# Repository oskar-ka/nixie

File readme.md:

# Features
- 6x IN-8
- 2/4x NE-2
- GPS disciplined, temperature compensated crystal oscillator
- Lysnetspænding i EU kan lovligt variere mellem 207Vac til 253Vac, som giver halveret DC på 146-182Vdc
- Automatisk lysstyrkedæmpning
- Temperaturføler
- Komponenter skal virke ved 85C (varm dag &leq;40C+4W*10K/W=80C)

# Strømforsyning
Nixie uret skal bruge to spændinger for at fungere: 5Vdc til microcontroller og logiske kredse, samt 180Vdc til at trække nixierørene. Hvert rør kan tåle op til 3.5mA, så med 6 rør skal strømforsyningen levere 21mA + lidt til de 4 små nixie prikker, så i alt maks. 30mA v. 180Vdc. Det er nok ikke nødvendigt med PFC ved 30mA, men det kunne måske være sjovt at lave hvis der er plads til det. Evt. kan strøforsyningen blive lavet på et separat print, som kan placeres under nixie-printet, så burde der være masser af plads. Skal den kunne skifte mellem 230Vac og 120Vac, og skal den gøre det automatisk?

### Specifikationer
- Fra IN-8 datablad:
    - Ignition voltage: &leq; 170V
    - Indication current: &leq; 2.5mA
    - Turn-off voltage: ??
- NE-2 lampe:
    - &lt;1mA
- 180Vdc, 20mA
- Current limiting, [foldback](https://www.eeeguide.com/foldback-current-limiting-circuit/)

### Der findes mange forskellige måder at opnå disse to spændinger:
- 12/24Vdc indgang &rarr; DC-DC til 5V + boost converter til 180Vdc
    - [Recom R12-150B](https://www.tme.eu/dk/en/details/r12-150b/dc-dc-converters/recom/)
- 230Vac indgang &rarr; diodebro som giver 325Vdc, med den rigtige modstand før 
nixierørene kan denne spænding bruges direkte; 5V AC-DC
    - Rimelig ueffektivt og ikke så sejt, men meget nemt
    - Nixiestrøm afhængig af netspænding
- 230Vac &rarr; styret thyristorbro som giver 180Vdc direkte; 5V AC-DC
    - Thyristorbroer er som regel store, ved ikke om man kan få en i DIP
- 230Vac &rarr; styret MOSFET ensretter som giver 180Vdc direkte; 5V AC-DC
    - Mere effektiv end thyristorbro
    - Skal bruge to MOSFETS hver vej for at kunne blokere = 8 MOSFETS
    - Kan evt. også laves som halvbølgeensretter, da den ikke skal levere ret meget strøm
- ~~230Vac &rarr; halveringstransformer 230V&rarr;115Vac &rarr; ensretter (styret/ikke styret); & 5V AC-DC~~
    - ~~Ret nemt, få komponenter, ret effektivt, galvanisk adskillelse~~
    - ~~Giver 160Vdc v. 230Vac, hvilket er fint, men hvis nettet går ned til 207Vdc så har vi kun 146Vdc hvilket ikke helt er nok~~
- 230Vac &rarr; 2/3-transformer = 195/217/239Vdc (min, nom, max)
    - enten direkte til nixierør, kunne sikkert fungere
        - Her vil varmetab være i modstande og måske IC, bedre at have det centreret i en NPN med varmeplade
    - eller transistor med varmetab
        - skal smide mellem 15-59V
        - ved 20mA &rarr; 0.3W-1.2W
        - TO-92: [PHE13003A](https://mou.sr/43Gdbwc) 60K/W, nogle af dem måske op til 2W??
        - TO-252 [MJD340](https://mou.sr/4o38ar5): 8.3K/W op til 15W
        - TO-220 [BUL741](https://mou.sr/3Q8gnh7): 2K/W op til 60W
        - TO-3 [MJ15024](https://mou.sr/4uGqn01): 0.7K/W op til 250W
    - eller buck-converter?
- 230Vac &rarr; reguleret flyback converter med 2 udgange!!
    - Ret sej løsning, galvanisk adskillelse, høj virkningsgrad, ikke nemt.
    - 

Skal power supply være på et separat print?

### Varmeplader
- Fischer Eletronik SK 13
    - 17 K/W
    - Lille U-formet, mindste heatsink som kan bruges
    - Højde: 13mm
- Mindste PCB mount
    - [link](https://www.digikey.com/en/products/detail/boyd-laconia-llc/581002B02500G/1216391)
    - 17.4 K/W
    - Højde: 25.4mm
- Fischer Elektronik SK 64
    - 2.7 K/W
    - Fås i [sort](https://www.digikey.com/en/products/detail/fischer-elektronik/SK-64-37-5-SA-1-x-M3-TO-220/25827581) eller [natural](https://www.digikey.com/en/products/detail/fischer-elektronik/SK-64-37-5-ME-1-x-M3-TO-220/25828864)
    - Højde: 25mm
- [SK 65](https://fischerelektronik.de/web_fischer/en/heatsinks/A01/Standard%20extruded%20heatsinks/$catalogue/fischerData/PR/SK65_/search.xhtml) Til SOT-32 transistor, lidt lavere end SK 64
- [U-formet](https://fischerelektronik.de/web_fischer/en/heatsinks/A07/U-Extruded%20heatsinks/$catalogue/fischerData/PR/ICK35_SA_/search.xhtml), lidt større end den jeg har, 15K/W
- ~~[SK 36](https://fischerelektronik.de/web_fischer/en/heatsinks/A01/Standard%20extruded%20heatsinks/$catalogue/fischerData/PR/SK36_/search.xhtml) Sej en til TO-3~~
- [SK 31](https://fischerelektronik.de/web_fischer/en/heatsinks/A01/Standard%20extruded%20heatsinks/$catalogue/fischerData/PR/SK31_/search.xhtml) Til TO-3, kun 12mm høj
- [SK 145](https://www.fischerelektronik.de/web_fischer/en_GB/heatsinks/A01/Standard%20extruded%20heatsinks/$catalogue/fischerData/PR/SK145_/search.xhtml)
- SK 59
- SK 09
- Adam tech
    - HSK-53-01 Højde: 18.5mm
    - HSK-55-01 Højde: 18.5mm
- [680-5A](https://mou.sr/4eQcQgR)
    - 12.7mm højde
    - 46x46mm footprint

### Komponenter
- AC Sikring + sikringsholder
    - 100mA glassikring?
- Transformer:
    - [Hammond 229A230](https://www.digikey.com/en/products/detail/hammond-manufacturing/229A230/454947) Unhoused
        - Height: 21.6mm
    - [Bel Signal IF-6-230](https://mou.sr/49APmcG) Red housing
        - Height: 22.6mm
    - [Bel Signal 230-25-LPI](https://mou.sr/4x3g8o8) Black housing
        - Height: 22.7mm
    - [Bel Signal LP-230-25](https://mou.sr/4uTkMDK) Unhoused
        - Height: 21.6mm
- 5V supply:
    - [Mean Well IRM-01-5](https://mou.sr/4u9H5E1)
    - [PBO-3E/F](https://www.belfuse.com/products/power-supplies/ac-dc-converters)
    - [PSK-5E](https://www.belfuse.com/products/power-supplies/ac-dc-converters/psk-5e-series)
    - [TRACO Power TMPS 05-105](https://mou.sr/49ALLeS) 1x1"
    - [Mornsun LS05-23B05DR3](https://www.mornsun-power.com/html/pdf/LS05-23B05DR3.html) Very small
- Ensretter IC
    - sdf

# Timekeeping
Forskellige niveauer af præcision: MCUens interne RC oscillator, normal kvartskrystal, temperaturkonpenseret krystaloscillator (TCXO), ovnkontrolleret krystaloscillator (OCXO). Desuden kan en oscillator *disciplineres* mht. et præcist eksternt signal, f.eks. GPS for en stor forbedring i stabilitet.

Stratum 3??

- OCXO
    - [CTS 139VGEVS10M000](https://mou.sr/4afKvxZ)
    - Bruger en lille "ovn" til at opvarme krystallen og holde dens temperatur stabil
- TCXO
    - Typisk tilgændelige i 280ppb, hvilket er super
    - De har god temperaturstabilitet, men ikke nødvedigvis god *aging*
    - MEMS vs quartz. MEMS har bedre aging, bedre temperaturforudsigelighed, bedre dynamisk stabilitet (når temp. ændrer sig), lavere fejlrater. De er dog dyrere, har mere fasestøj, og bruger mere strøm.
    - [SiTime MEMS](https://www.sitime.com/products/ultrastable-mhz-super-tcxos/super-tcxos/sit5356)

Vi vil gerne under 1s afvigelse over et år uden GPS, dette 

# Udførsel, lagkagekasse
Bruger den første kasse der blev bygget, den laserskårede. 
6 IN-8 rør, 2 NE-2 lamper. Ingen optokoblere. 
Forsynet med 170V reguleret direkte fra ensrettet mains, derudover lille indpakket 5V AC-DC forsyning. 
Forsyning på separat print, som hænger under styreprint med 20mm standoffs, og bruger disse til forbindelse.
Ensretter, CRC filter, TO-3 transistor, (en cap mere?)
Strømindgang via IEC C7 stik uden ground, intet at bruge det til.

# Komponenter, generel
- Lamper
    - 6x IN-8
    - 2/4x NE-2
- Forsyningsprint
    - Sikring
        - 100mA
    - Transformer
    - Ensretter
    - Lyt
    - Zenerdiode(r)
        - hvis 180V så 5W
    - Effekttransistor
    - OCP transistor
    - Modstande
    - AC-DC forsyning
- Styreprint
    - ATtiny2313 x1
    - Shift register x4
    - Quad optokobler f.eks. LTV-845M x4
    - SN74141 x4
    - MPSA42 NPN transistor
    - 6x Anodemodstande til nixierør 1/2W
    - 2x Anodemodstande til NE2 lamper 1/4W

# Enclosure
### Varmeafgivelse
- Original laserskåret lagkagekasse
    - Test 1: P=4W, UT=22C, IT=67C &rarr; +45C v. 4W = 11.25 K/W
    - Test 2: P=3W, UT=22C, IT=58C &rarr; +36C v. 3W = 12    K/W
    - Test 3: P=2W, UT=22C, IT=49C &rarr; +26C v. 2W = 13.5  K/W
    - Test 4: P=1W, UT=22C, IT=38C &rarr; +16C v. 1W = 16    K/W
    
SMD keramiske kondensatorer 2.2uF 450V [her](https://mou.sr/4eBqHqi)

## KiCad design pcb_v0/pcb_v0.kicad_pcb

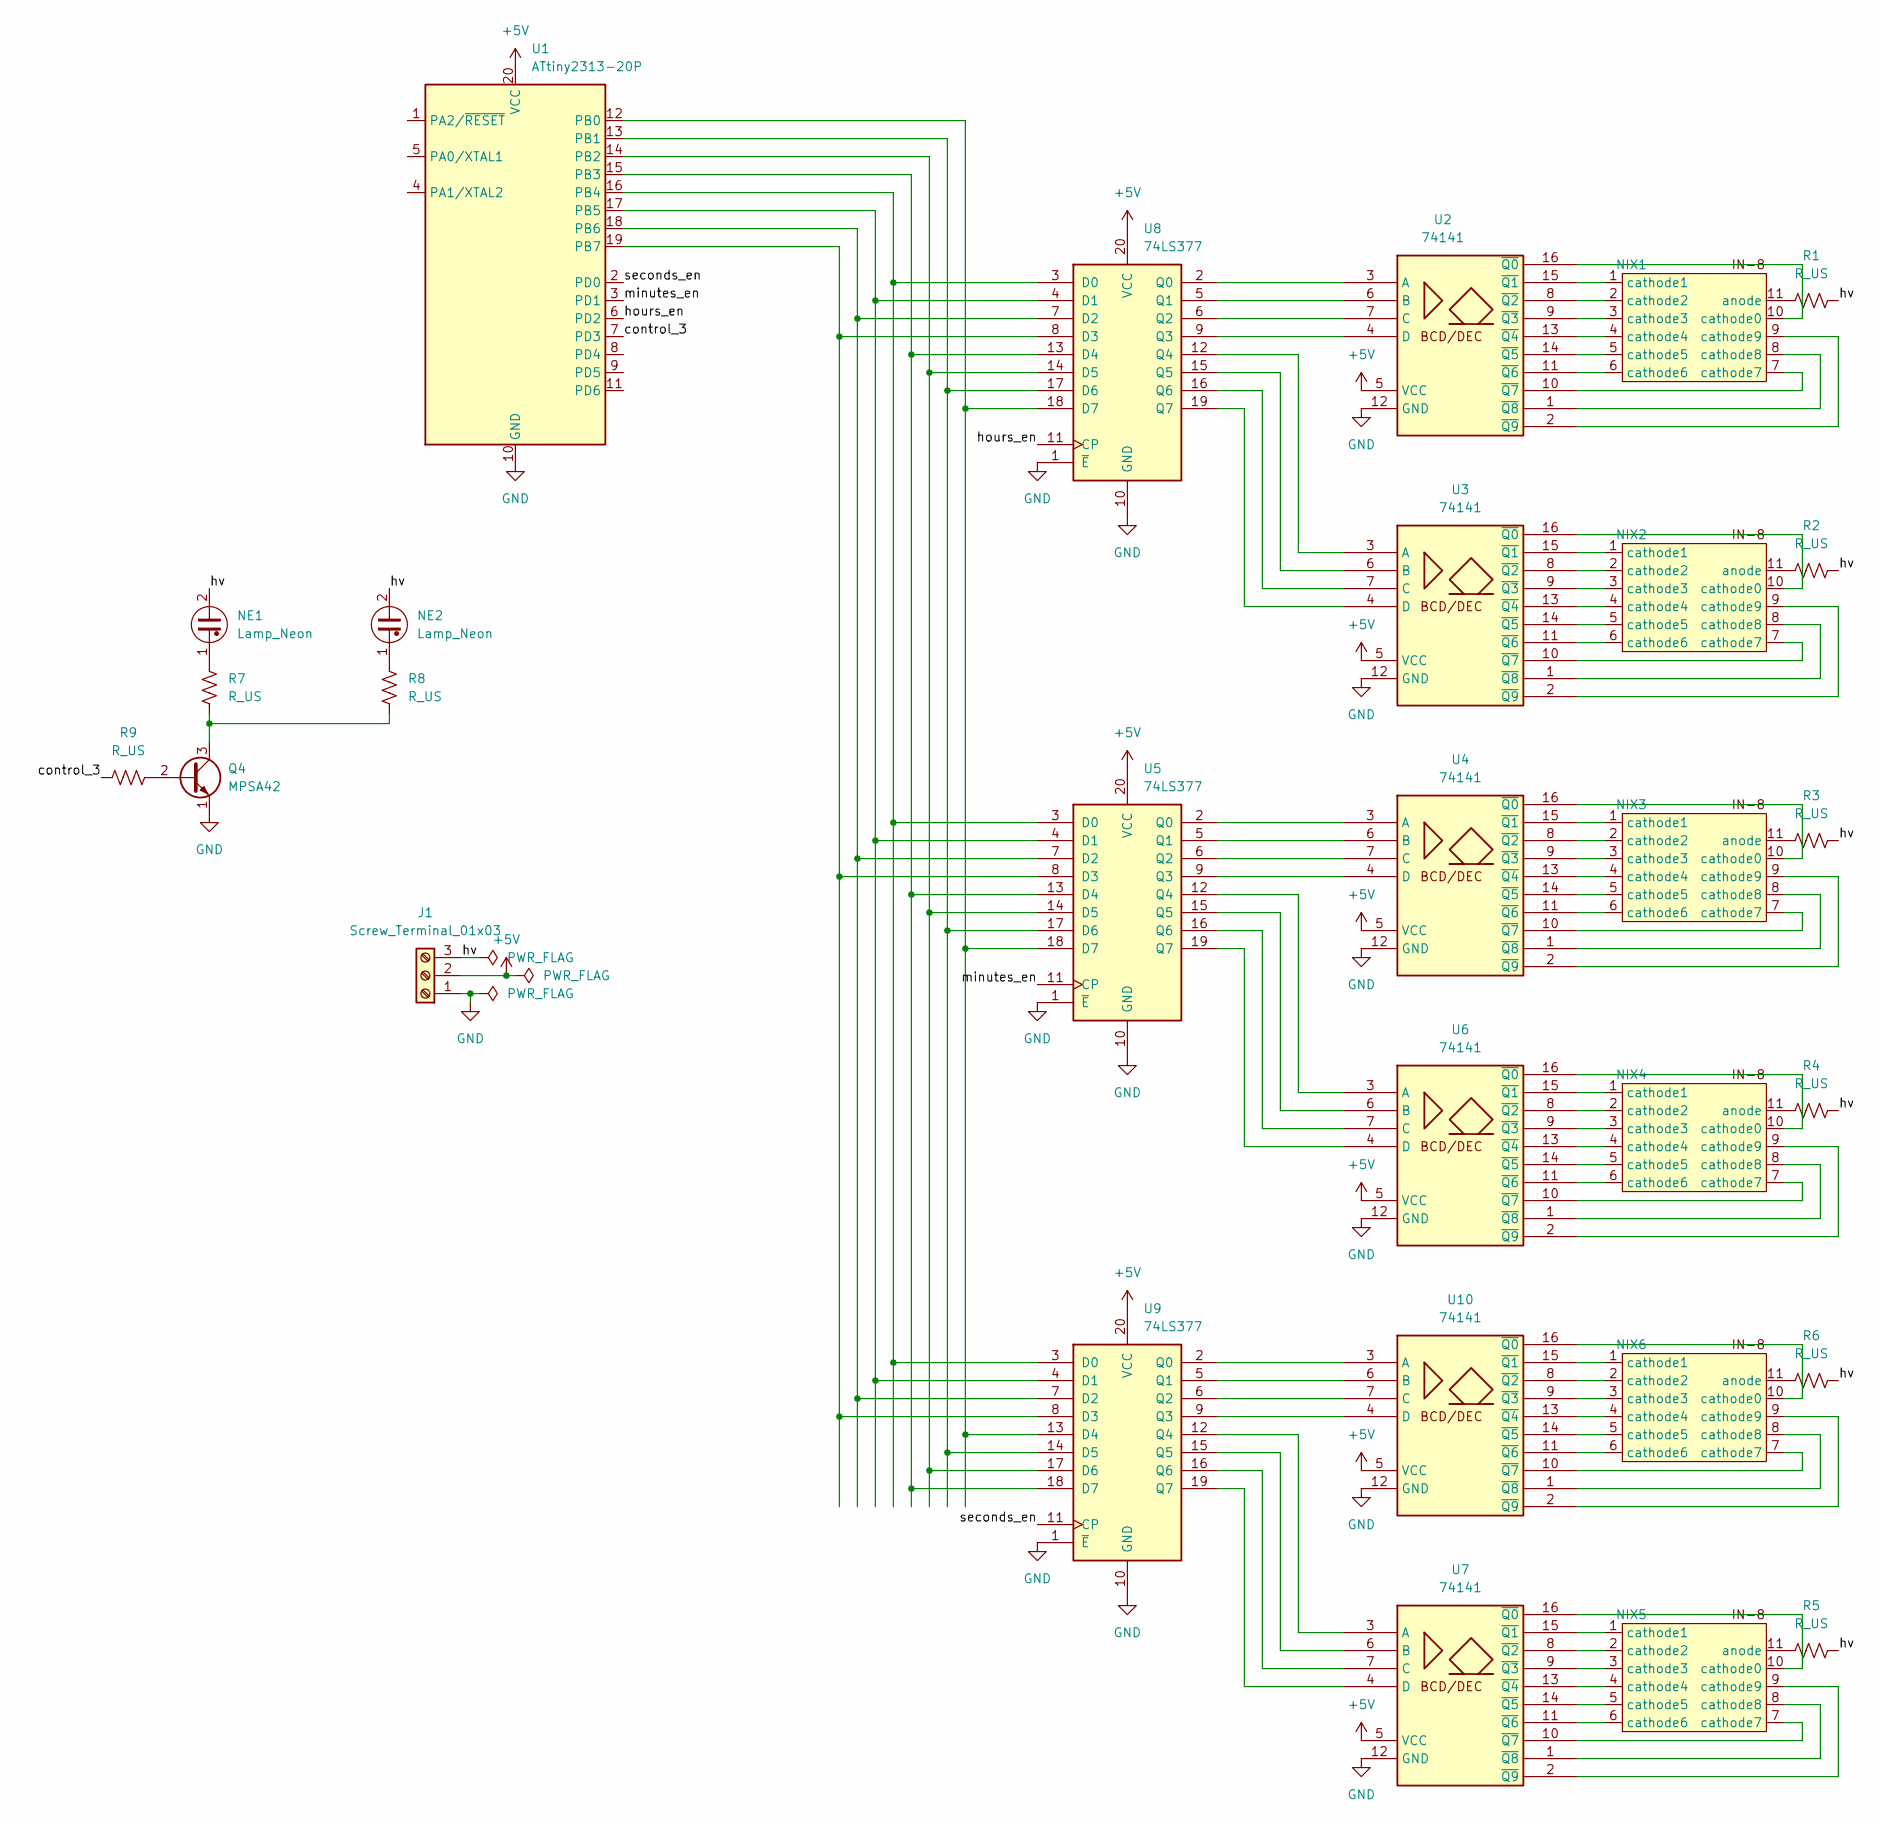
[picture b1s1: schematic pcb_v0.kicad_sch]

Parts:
J1: Screw_Terminal_01x03; PinHeader_1x03_P2.54mm_Vertical
NE1, NE2: Lamp_Neon; PinSocket_1x02_P1.27mm_Vertical
NIX1, NIX2, NIX3, NIX4, NIX5, NIX6: in-8
Q4: MPSA42; TO-92_Inline
R1, R2, R3, R4, R5, R6: R_US; R_Axial_DIN0309_L9.0mm_D3.2mm_P12.70mm_Horizontal
R7, R8, R9: R_US; R_Axial_DIN0207_L6.3mm_D2.5mm_P7.62mm_Horizontal
U1: ATtiny2313-20P; DIP-20_W7.62mm
U2, U3, U4, U6, U7, U10: 74141; DIP-16_W7.62mm
U5, U8, U9: 74LS377; DIP-20_W7.62mm

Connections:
+5V: J1.2, U1.20 (VCC), U2.5 (VCC), U3.5 (VCC), U4.5 (VCC), U5.20 (VCC), U6.5 (VCC), U7.5 (VCC), U8.20 (VCC), U9.20 (VCC), U10.5 (VCC)
/control_3: R9.2, U1.7 (PD3)
/hours_en: U1.6 (PD2), U8.11 (CP)
/hv: J1.3, NE1.2, NE2.2, R1.2, R2.2, R3.2, R4.2, R5.2, R6.2
/minutes_en: U1.3 (PD1), U5.11 (CP)
/seconds_en: U1.2 (PD0), U9.11 (CP)
GND: J1.1, Q4.1 (E), U1.10 (GND), U2.12 (GND), U3.12 (GND), U4.12 (GND), U5.1 (~E), U5.10 (GND), U6.12 (GND), U7.12 (GND), U8.1 (~E), U8.10 (GND), U9.1 (~E), U9.10 (GND), U10.12 (GND)
unnamed: NE1.1, R7.2
unnamed: NE2.1, R8.2
unnamed: NIX1.11 (anode), R1.1
unnamed: NIX1.10 (cathode0), U2.16 (~Q0)
unnamed: NIX1.1 (cathode1), U2.15 (~Q1)
unnamed: NIX1.2 (cathode2), U2.8 (~Q2)
unnamed: NIX1.3 (cathode3), U2.9 (~Q3)
unnamed: NIX1.4 (cathode4), U2.13 (~Q4)
unnamed: NIX1.5 (cathode5), U2.14 (~Q5)
unnamed: NIX1.6 (cathode6), U2.11 (~Q6)
unnamed: NIX1.7 (cathode7), U2.10 (~Q7)
unnamed: NIX1.8 (cathode8), U2.1 (~Q8)
unnamed: NIX1.9 (cathode9), U2.2 (~Q9)
unnamed: NIX2.11 (anode), R2.1
unnamed: NIX2.10 (cathode0), U3.16 (~Q0)
unnamed: NIX2.1 (cathode1), U3.15 (~Q1)
unnamed: NIX2.2 (cathode2), U3.8 (~Q2)
unnamed: NIX2.3 (cathode3), U3.9 (~Q3)
unnamed: NIX2.4 (cathode4), U3.13 (~Q4)
unnamed: NIX2.5 (cathode5), U3.14 (~Q5)
unnamed: NIX2.6 (cathode6), U3.11 (~Q6)
unnamed: NIX2.7 (cathode7), U3.10 (~Q7)
unnamed: NIX2.8 (cathode8), U3.1 (~Q8)
unnamed: NIX2.9 (cathode9), U3.2 (~Q9)
unnamed: NIX3.11 (anode), R3.1
unnamed: NIX3.10 (cathode0), U4.16 (~Q0)
unnamed: NIX3.1 (cathode1), U4.15 (~Q1)
unnamed: NIX3.2 (cathode2), U4.8 (~Q2)
unnamed: NIX3.3 (cathode3), U4.9 (~Q3)
unnamed: NIX3.4 (cathode4), U4.13 (~Q4)
unnamed: NIX3.5 (cathode5), U4.14 (~Q5)
unnamed: NIX3.6 (cathode6), U4.11 (~Q6)
unnamed: NIX3.7 (cathode7), U4.10 (~Q7)
unnamed: NIX3.8 (cathode8), U4.1 (~Q8)
unnamed: NIX3.9 (cathode9), U4.2 (~Q9)
unnamed: NIX4.11 (anode), R4.1
unnamed: NIX4.10 (cathode0), U6.16 (~Q0)
unnamed: NIX4.1 (cathode1), U6.15 (~Q1)
unnamed: NIX4.2 (cathode2), U6.8 (~Q2)
unnamed: NIX4.3 (cathode3), U6.9 (~Q3)
unnamed: NIX4.4 (cathode4), U6.13 (~Q4)
unnamed: NIX4.5 (cathode5), U6.14 (~Q5)
unnamed: NIX4.6 (cathode6), U6.11 (~Q6)
unnamed: NIX4.7 (cathode7), U6.10 (~Q7)
unnamed: NIX4.8 (cathode8), U6.1 (~Q8)
unnamed: NIX4.9 (cathode9), U6.2 (~Q9)
unnamed: NIX5.11 (anode), R5.1
unnamed: NIX5.10 (cathode0), U7.16 (~Q0)
unnamed: NIX5.1 (cathode1), U7.15 (~Q1)
unnamed: NIX5.2 (cathode2), U7.8 (~Q2)
unnamed: NIX5.3 (cathode3), U7.9 (~Q3)
unnamed: NIX5.4 (cathode4), U7.13 (~Q4)
unnamed: NIX5.5 (cathode5), U7.14 (~Q5)
unnamed: NIX5.6 (cathode6), U7.11 (~Q6)
unnamed: NIX5.7 (cathode7), U7.10 (~Q7)
unnamed: NIX5.8 (cathode8), U7.1 (~Q8)
unnamed: NIX5.9 (cathode9), U7.2 (~Q9)
unnamed: NIX6.11 (anode), R6.1
unnamed: NIX6.10 (cathode0), U10.16 (~Q0)
unnamed: NIX6.1 (cathode1), U10.15 (~Q1)
unnamed: NIX6.2 (cathode2), U10.8 (~Q2)
unnamed: NIX6.3 (cathode3), U10.9 (~Q3)
unnamed: NIX6.4 (cathode4), U10.13 (~Q4)
unnamed: NIX6.5 (cathode5), U10.14 (~Q5)
unnamed: NIX6.6 (cathode6), U10.11 (~Q6)
unnamed: NIX6.7 (cathode7), U10.10 (~Q7)
unnamed: NIX6.8 (cathode8), U10.1 (~Q8)
unnamed: NIX6.9 (cathode9), U10.2 (~Q9)
unnamed: Q4.2 (B), R9.1
unnamed: Q4.3 (C), R7.1, R8.1
unnamed: U1.12 (PB0), U5.18 (D7), U8.18 (D7), U9.13 (D4)
unnamed: U1.13 (PB1), U5.17 (D6), U8.17 (D6), U9.14 (D5)
unnamed: U1.14 (PB2), U5.14 (D5), U8.14 (D5), U9.17 (D6)
unnamed: U1.15 (PB3), U5.13 (D4), U8.13 (D4), U9.18 (D7)
unnamed: U1.16 (PB4), U5.3 (D0), U8.3 (D0), U9.3 (D0)
unnamed: U1.17 (PB5), U5.4 (D1), U8.4 (D1), U9.4 (D1)
unnamed: U1.18 (PB6), U5.7 (D2), U8.7 (D2), U9.7 (D2)
unnamed: U1.19 (PB7), U5.8 (D3), U8.8 (D3), U9.8 (D3)
unnamed: U2.3 (A), U8.2 (Q0)
unnamed: U2.6 (B), U8.5 (Q1)
unnamed: U2.7 (C), U8.6 (Q2)
unnamed: U2.4 (D), U8.9 (Q3)
unnamed: U3.3 (A), U8.12 (Q4)
unnamed: U3.6 (B), U8.15 (Q5)
unnamed: U3.7 (C), U8.16 (Q6)
unnamed: U3.4 (D), U8.19 (Q7)
unnamed: U4.3 (A), U5.2 (Q0)
unnamed: U4.6 (B), U5.5 (Q1)
unnamed: U4.7 (C), U5.6 (Q2)
unnamed: U4.4 (D), U5.9 (Q3)
unnamed: U5.12 (Q4), U6.3 (A)
unnamed: U5.15 (Q5), U6.6 (B)
unnamed: U5.16 (Q6), U6.7 (C)
unnamed: U5.19 (Q7), U6.4 (D)
unnamed: U7.3 (A), U9.12 (Q4)
unnamed: U7.6 (B), U9.15 (Q5)
unnamed: U7.7 (C), U9.16 (Q6)
unnamed: U7.4 (D), U9.19 (Q7)
unnamed: U9.2 (Q0), U10.3 (A)
unnamed: U9.5 (Q1), U10.6 (B)
unnamed: U9.6 (Q2), U10.7 (C)
unnamed: U9.9 (Q3), U10.4 (D)

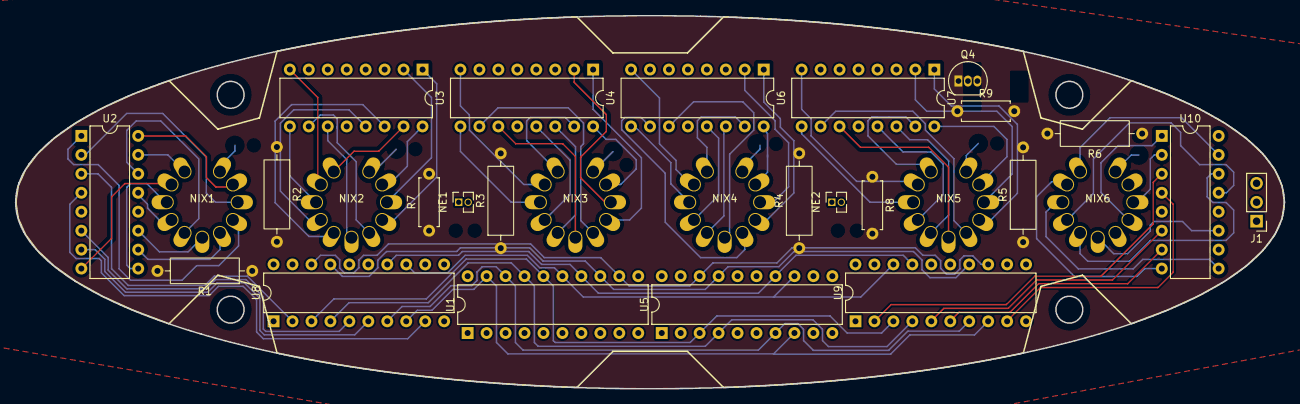
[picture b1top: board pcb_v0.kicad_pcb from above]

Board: 2 copper layers, 170.0 x 50.0 mm, 29 parts (0 on the bottom side), 109 nets.

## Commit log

2022-12-29 Added files
2022-12-29 Boost converter w push-pull
2023-01-22 Deleted old files
2023-01-22 Added up-to-date files
2023-01-23 Its aliiiive2
2023-01-28 save
2023-01-28 New folder
2023-01-28 Created kiCAD project
2023-01-29 saved
2023-01-29 Added inductor files
2023-01-30 Schem from ltspice to kicad
2023-12-22 added files for new circuit
2023-12-30 created new kicad project
2024-01-07 Added symbols for 74141 and in-8
2024-01-08 Untrack ignored files
2024-01-08 Updated gitignore
2024-01-08 Correctly removed untracked files
2024-01-12 ATtiny and flip flops routed
2024-01-12 new outline, now nothing fits
2024-01-12 registers wired correctly this time
2026-05-13 Add readme and datasheet
2026-05-13 PSU discussion
2026-06-22 SMD cap
